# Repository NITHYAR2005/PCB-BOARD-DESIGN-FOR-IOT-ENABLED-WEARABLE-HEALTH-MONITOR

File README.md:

View this project on [CADLAB.io](https://cadlab.io/project/29229). 

# PCB-BOARD-DESIGN-FOR-IOT-ENABLED-WEARABLE-HEALTH-MONITOR

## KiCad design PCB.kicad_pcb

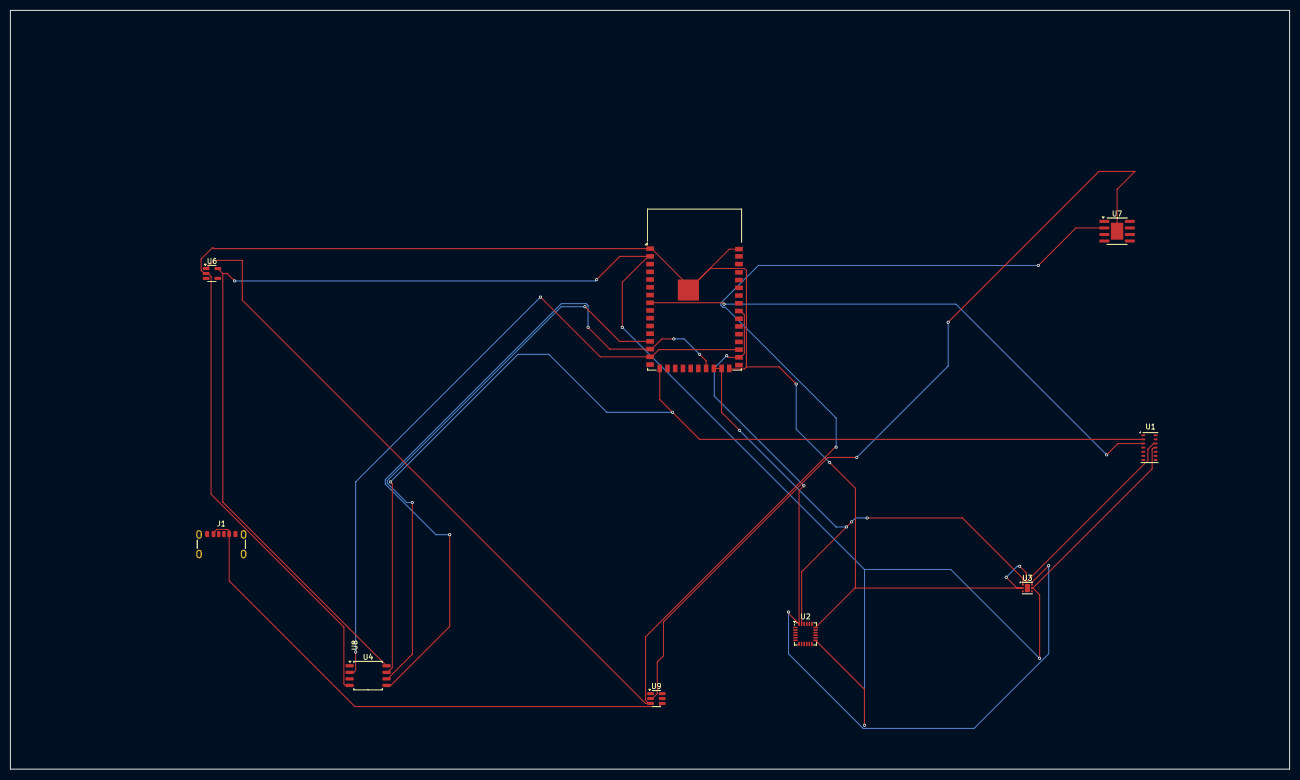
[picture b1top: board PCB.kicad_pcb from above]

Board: 2 copper layers, 248.2 x 147.2 mm, 9 parts (0 on the bottom side), 12 nets.

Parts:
J1: USB_C_Receptacle_PowerOnly_6P; USB_C_Receptacle_GCT_USB4125-xx-x-0190_6P_TopMnt_Horizontal
U1: MAX30102; Maxim_OLGA-14_3.3x5.6mm_P0.8mm
U2: MPU-6050; InvenSense_QFN-24_4x4mm_P0.5mm
U3: TMP117xxDRV; WSON-6-1EP_2x2mm_P0.65mm_EP1x1.6mm
U4: W25Q32JVSS; SOIC-8_5.3x5.3mm_P1.27mm
U6: AP2112K-3.3; SOT-23-5
U7: LGS5500EP; SOIC-8-1EP_3.9x4.9mm_P1.27mm_EP2.41x3.3mm
U8: ESP32-S2-WROVER-I; ESP32-S2-WROVER
U9: TP4057; TSOT-23-6

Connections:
+3.3V: U1.11 (VDD), U2.13 (VDD), U3.5 (V+), U4.8 (VCC), U6.5 (VOUT), U8.2 (3V3)
GND: U1.12 (GND), U2.18 (GND), U3.2 (GND), U4.4 (GND), U6.2 (GND), U8.1 (GND), U8.26 (GND), U8.42 (GND), U8.43 (GND)
unnamed: U1.2 (SCL), U4.7 (~HOLD/~RESET/IO_{3}), U8.17 (IO14)
unnamed: U1.3 (SDA), U8.8 (IO05)
unnamed: U2.23 (SCL), U3.1 (SCL), U8.24 (IO21), U8.25 (IO26)
unnamed: U2.24 (SDA), U3.6 (SDA), U8.28 (IO34), U8.34 (IO40)
unnamed: U4.6 (CLK), U8.13 (IO10)
unnamed: U4.5 (DI/IO_{0}), U8.14 (IO11), U8.23 (USB_D+)
unnamed: U4.2 (DO/IO_{1}), U8.15 (IO12), U8.29 (IO35)
unnamed: U6.1 (VIN), U7.2 (VIN), U9.3 (BAT)
unnamed: U7.9 (GND), U9.2 (GND)
unnamed: J1.A9 (VBUS), J1.B9 (VBUS), U9.4 (V_{CC})

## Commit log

2025-04-10 Backlink to CADLAB.io has been added.
